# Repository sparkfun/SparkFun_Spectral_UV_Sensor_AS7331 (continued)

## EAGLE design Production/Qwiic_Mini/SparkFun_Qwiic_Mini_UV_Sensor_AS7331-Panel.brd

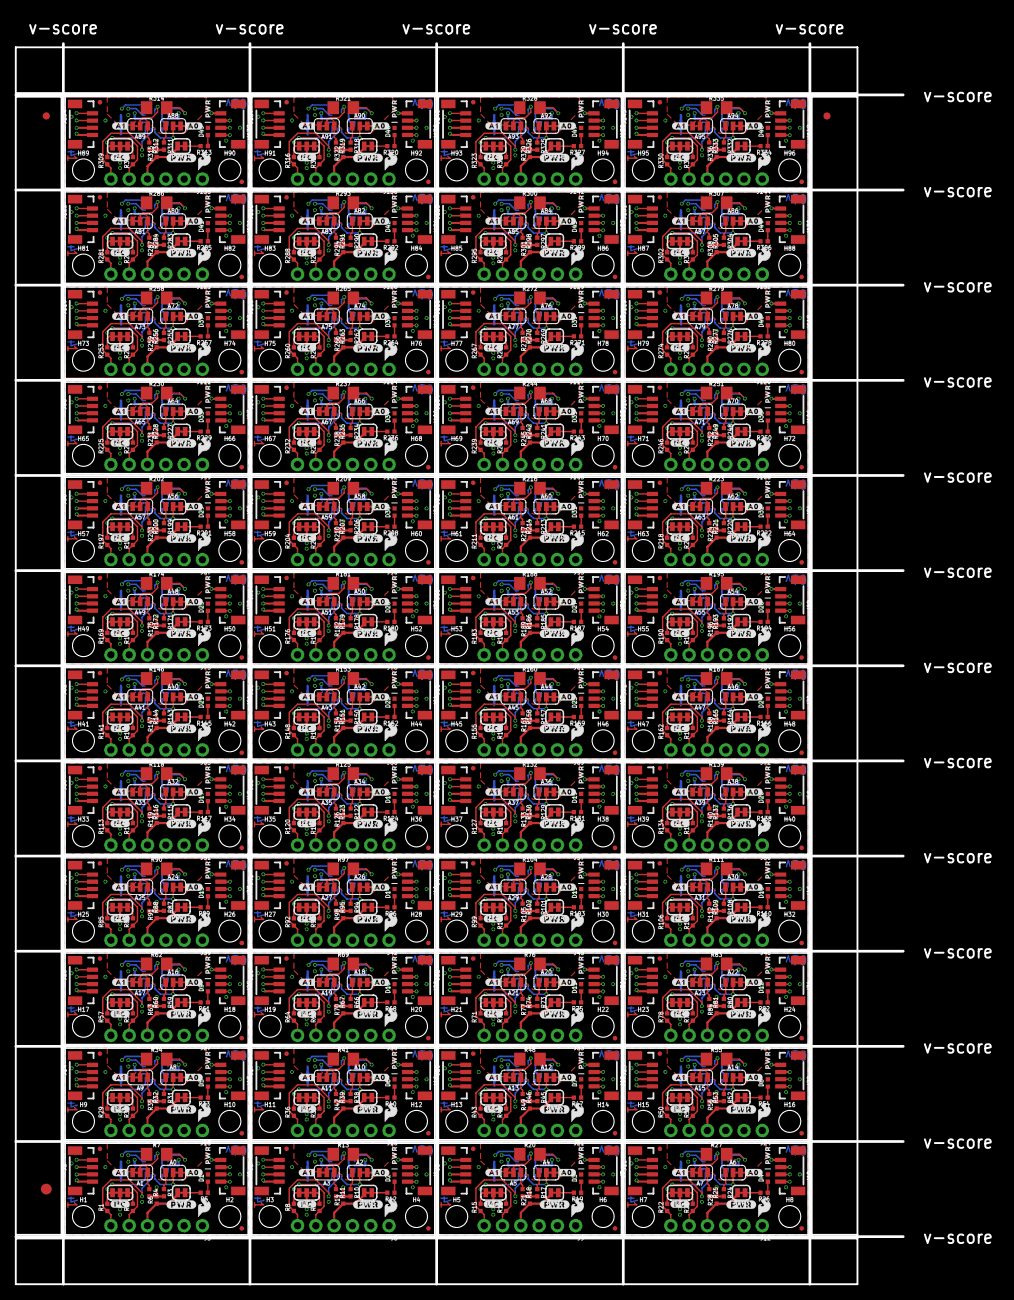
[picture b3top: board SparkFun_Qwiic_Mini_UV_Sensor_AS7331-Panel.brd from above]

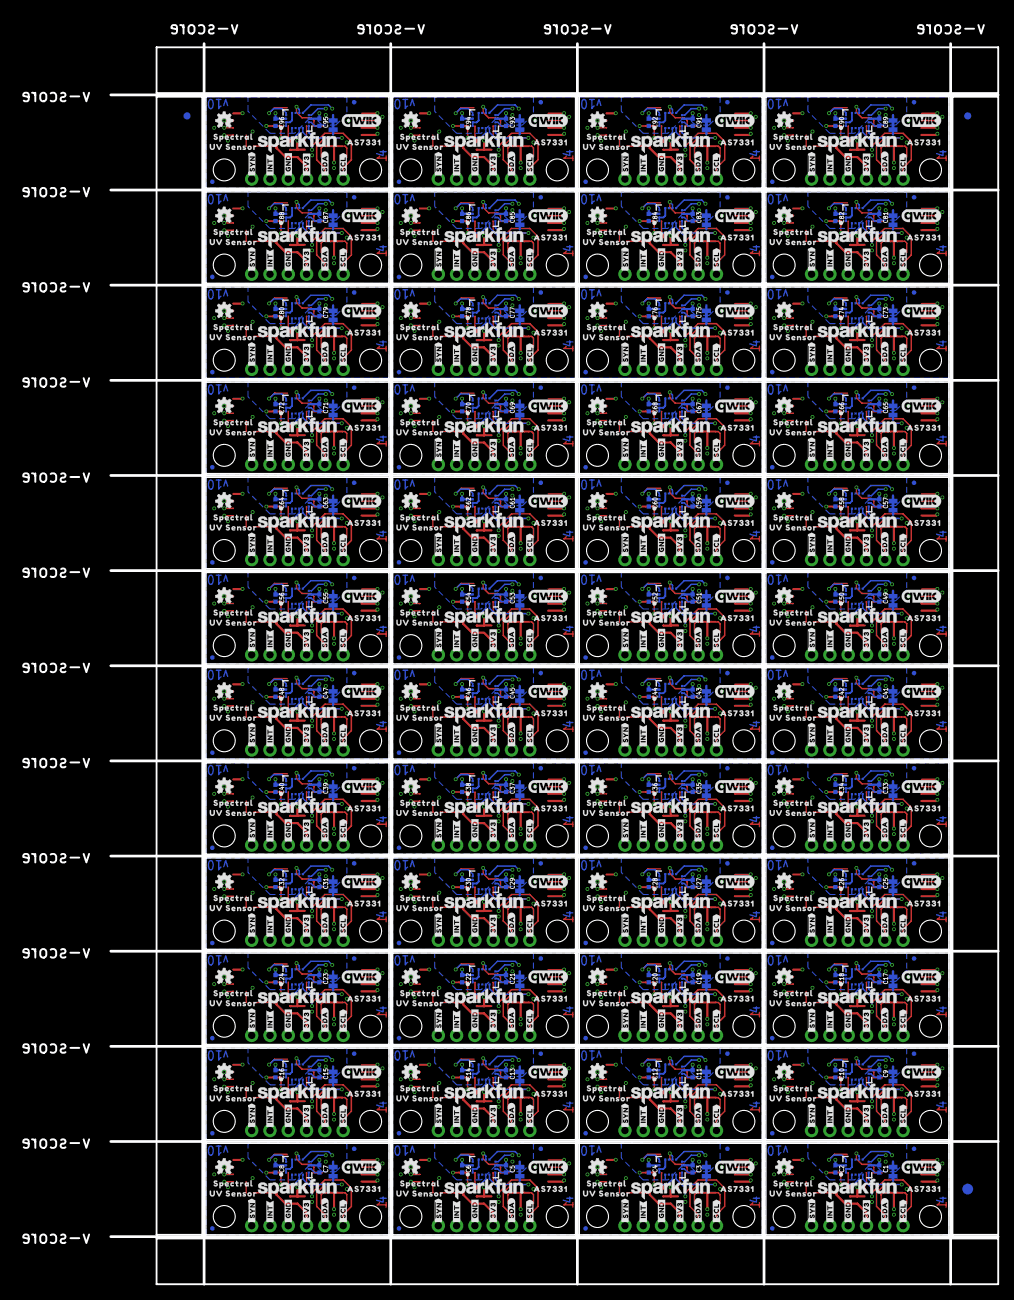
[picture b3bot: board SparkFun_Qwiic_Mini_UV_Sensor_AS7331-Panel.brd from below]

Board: 4 copper layers, 123.2 x 172.2 mm, 2070 parts (867 on the bottom side), 816 nets.

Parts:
A0, A1, A2, A3, A4, A5, A6, A7, A8, A9, A10, A11, A12, A13, A14, A15, A16, A17, A18, A19, A20, A21, A22, A23, A24, A25, A26, A27, A28, A29, A30, A31, A32, A33, A34, A35, A36, A37, A38, A39, A40, A41, A42, A43, A44, A45, A46, A47, A48, A49, A50, A51, A52, A53, A54, A55, A56, A57, A58, A59, A60, A61, A62, A63, A64, A65, A66, A67, A68, A69, A70, A71, A72, A73, A74, A75, A76, A77, A78, A79, A80, A81, A82, A83, A84, A85, A86, A87, A88, A89, A90, A91, A92, A93, A94, A95: JUMPER-SMT_3_1-NC_TRACE_SILK; SMT-JUMPER_3_1-NC_TRACE_SILK
C1, C2, C3, C4, C5, C6, C7, C8, C9, C10, C11, C12, C13, C14, C15, C16, C17, C18, C19, C20, C21, C22, C23, C24, C25, C26, C27, C28, C29, C30, C31, C32, C33, C34, C35, C36, C37, C38, C39, C40, C41, C42, C43, C44, C45, C46, C47, C48, C49, C50, C51, C52, C53, C54, C55, C56, C57, C58, C59, C60, C61, C62, C63, C64, C65, C66, C67, C68, C69, C70, C71, C72, C73, C74, C75, C76, C77, C78, C79, C80, C81, C82, C83, C84, C85, C86, C87, C88, C89, C90, C91, C92, C93, C94, C95, C96: 0.1uF; 0402-TIGHT
D1, D2, D3, D4, D5, D6, D7, D8, D9, D10, D11, D12, D13, D14, D15, D16, D17, D18, D19, D20, D21, D22, D23, D24, D25, D26, D27, D28, D29, D30, D31, D32, D33, D34, D35, D36, D37, D38, D39, D40, D41, D42, D43, D44, D45, D46, D47, D48: RED; LED-0402
E$1, E$2, E$3, E$4: FIDUCIAL-1X2
E$5, E$6: FIDUCIAL-1.5X3
FD1, FD2, FD3, FD4, FD5, FD6, FD7, FD8, FD9, FD10, FD11, FD12, FD13, FD14, FD15, FD16, FD17, FD18, FD19, FD20, FD21, FD22, FD23, FD24, FD25, FD26, FD27, FD28, FD29, FD30, FD31, FD32, FD33, FD34, FD35, FD36, FD37, FD38, FD39, FD40, FD41, FD42, FD43, FD44, FD45, FD46, FD47, FD48, FD49, FD50, FD51, FD52, FD53, FD54, FD55, FD56, FD57, FD58, FD59, FD60, FD61, FD62, FD63, FD64, FD65, FD66, FD67, FD68, FD69, FD70, FD71, FD72, FD73, FD74, FD75, FD76, FD77, FD78, FD79, FD80, FD81, FD82, FD83, FD84, FD85, FD86, FD87, FD88, FD89, FD90, FD91, FD92, FD93, FD94, FD95, FD96, FD97, FD98, FD99, FD100, FD101, FD102, FD103, FD104, FD105, FD106, FD107, FD108, FD109, FD110, FD111, FD112, FD113, FD114, FD115, FD116, FD117, FD118, FD119, FD120, FD121, FD122, FD123, FD124, FD125, FD126, FD127, FD128, FD129, FD130, FD131, FD132, FD133, FD134, FD135, FD136, FD137, FD138, FD139, FD140, FD141, FD142, FD143, FD144, FD145, FD146, FD147, FD148, FD149, FD150, FD151, FD152, FD153, FD154, FD155, FD156, FD157, FD158, FD159, FD160, FD161, FD162, FD163, FD164, FD165, FD166, FD167, FD168, FD169, FD170, FD171, FD172, FD173, FD174, FD175, FD176, FD177, FD178, FD179, FD180, FD181, FD182, FD183, FD184, FD185, FD186, FD187, FD188, FD189, FD190, FD191, FD192: FIDUCIALUFIDUCIAL; FIDUCIAL-MICRO
H1, H2, H3, H4, H5, H6, H7, H8, H9, H10, H11, H12, H13, H14, H15, H16, H17, H18, H19, H20, H21, H22, H23, H24, H25, H26, H27, H28, H29, H30, H31, H32, H33, H34, H35, H36, H37, H38, H39, H40, H41, H42, H43, H44, H45, H46, H47, H48, H49, H50, H51, H52, H53, H54, H55, H56, H57, H58, H59, H60, H61, H62, H63, H64, H65, H66, H67, H68, H69, H70, H71, H72, H73, H74, H75, H76, H77, H78, H79, H80, H81, H82, H83, H84, H85, H86, H87, H88, H89, H90, H91, H92, H93, H94, H95, H96: STAND-OFFTIGHT; STAND-OFF-TIGHT
I2C, I2C1, I2C2, I2C3, I2C4, I2C5, I2C6, I2C7, I2C8, I2C9, I2C10, I2C11, I2C12, I2C13, I2C14, I2C15, I2C16, I2C17, I2C18, I2C19, I2C20, I2C21, I2C22, I2C23, I2C24, I2C25, I2C26, I2C27, I2C28, I2C29, I2C30, I2C31, I2C32, I2C33, I2C34, I2C35, I2C36, I2C37, I2C38, I2C39, I2C40, I2C41, I2C42, I2C43, I2C44, I2C45, I2C46, I2C47: JUMPER-SMT_3_2-NC_TRACE_SILK; SMT-JUMPER_3_2-NC_TRACE_SILK
J1, J2, J4, J5, J7, J8, J10, J11, J13, J14, J16, J17, J19, J20, J22, J23, J25, J26, J28, J29, J31, J32, J34, J35, J37, J38, J40, J41, J43, J44, J46, J47, J49, J50, J52, J53, J55, J56, J58, J59, J61, J62, J64, J65, J67, J68, J70, J71, J73, J74, J76, J77, J79, J80, J82, J83, J85, J86, J88, J89, J91, J92, J94, J95, J97, J98, J100, J101, J103, J104, J106, J107, J109, J110, J112, J113, J115, J116, J118, J119, J121, J122, J124, J125, J127, J128, J130, J131, J133, J134, J136, J137, J139, J140, J142, J143: Qwiic Vert; JST04_1MM_VERT
J3, J6, J9, J12, J15, J18, J21, J24, J27, J30, J33, J36, J39, J42, J45, J48, J51, J54, J57, J60, J63, J66, J69, J72, J75, J78, J81, J84, J87, J90, J93, J96, J99, J102, J105, J108, J111, J114, J117, J120, J123, J126, J129, J132, J135, J138, J141, J144: 1X06_NO_SILK
LOGO1, LOGO5, LOGO9, LOGO13, LOGO17, LOGO21, LOGO25, LOGO29, LOGO33, LOGO37, LOGO41, LOGO45, LOGO49, LOGO53, LOGO57, LOGO61, LOGO65, LOGO69, LOGO73, LOGO77, LOGO81, LOGO85, LOGO89, LOGO93, LOGO97, LOGO101, LOGO105, LOGO109, LOGO113, LOGO117, LOGO121, LOGO125, LOGO129, LOGO133, LOGO137, LOGO141, LOGO145, LOGO149, LOGO153, LOGO157, LOGO161, LOGO165, LOGO169, LOGO173, LOGO177, LOGO181, LOGO185, LOGO189: SFE_LOGO_NAME.1_INCH; SFE_LOGO_NAME_.1
LOGO2, LOGO6, LOGO10, LOGO14, LOGO18, LOGO22, LOGO26, LOGO30, LOGO34, LOGO38, LOGO42, LOGO46, LOGO50, LOGO54, LOGO58, LOGO62, LOGO66, LOGO70, LOGO74, LOGO78, LOGO82, LOGO86, LOGO90, LOGO94, LOGO98, LOGO102, LOGO106, LOGO110, LOGO114, LOGO118, LOGO122, LOGO126, LOGO130, LOGO134, LOGO138, LOGO142, LOGO146, LOGO150, LOGO154, LOGO158, LOGO162, LOGO166, LOGO170, LOGO174, LOGO178, LOGO182, LOGO186, LOGO190: QWIIC_LOGO_CONNECTOR; QWIIC_5.5MM
LOGO3, LOGO7, LOGO11, LOGO15, LOGO19, LOGO23, LOGO27, LOGO31, LOGO35, LOGO39, LOGO43, LOGO47, LOGO51, LOGO55, LOGO59, LOGO63, LOGO67, LOGO71, LOGO75, LOGO79, LOGO83, LOGO87, LOGO91, LOGO95, LOGO99, LOGO103, LOGO107, LOGO111, LOGO115, LOGO119, LOGO123, LOGO127, LOGO131, LOGO135, LOGO139, LOGO143, LOGO147, LOGO151, LOGO155, LOGO159, LOGO163, LOGO167, LOGO171, LOGO175, LOGO179, LOGO183, LOGO187, LOGO191: OSHW-LOGOMINI; OSHW-LOGO-MINI
LOGO4, LOGO8, LOGO12, LOGO16, LOGO20, LOGO24, LOGO28, LOGO32, LOGO36, LOGO40, LOGO44, LOGO48, LOGO52, LOGO56, LOGO60, LOGO64, LOGO68, LOGO72, LOGO76, LOGO80, LOGO84, LOGO88, LOGO92, LOGO96, LOGO100, LOGO104, LOGO108, LOGO112, LOGO116, LOGO120, LOGO124, LOGO128, LOGO132, LOGO136, LOGO140, LOGO144, LOGO148, LOGO152, LOGO156, LOGO160, LOGO164, LOGO168, LOGO172, LOGO176, LOGO180, LOGO184, LOGO188, LOGO192: SFE_LOGO_FLAME.1_INCH; SFE_LOGO_FLAME_.1
PWR, PWR1, PWR2, PWR3, PWR4, PWR5, PWR6, PWR7, PWR8, PWR9, PWR10, PWR11, PWR12, PWR13, PWR14, PWR15, PWR16, PWR17, PWR18, PWR19, PWR20, PWR21, PWR22, PWR23, PWR24, PWR25, PWR26, PWR27, PWR28, PWR29, PWR30, PWR31, PWR32, PWR33, PWR34, PWR35, PWR36, PWR37, PWR38, PWR39, PWR40, PWR41, PWR42, PWR43, PWR44, PWR45, PWR46, PWR47: JUMPER-SMT_2_NC_TRACE_SILK; SMT-JUMPER_2_NC_TRACE_SILK
R1, R2, R5, R8, R9, R12, R15, R16, R19, R22, R23, R26, R29, R30, R33, R36, R37, R40, R43, R44, R47, R50, R51, R54, R57, R58, R61, R64, R65, R68, R71, R72, R75, R78, R79, R82, R85, R86, R89, R92, R93, R96, R99, R100, R103, R106, R107, R110, R113, R114, R117, R120, R121, R124, R127, R128, R131, R134, R135, R138, R141, R142, R145, R148, R149, R152, R155, R156, R159, R162, R163, R166, R169, R170, R173, R176, R177, R180, R183, R184, R187, R190, R191, R194, R197, R198, R201, R204, R205, R208, R211, R212, R215, R218, R219, R222, R225, R226, R229, R232, R233, R236, R239, R240, R243, R246, R247, R250, R253, R254, R257, R260, R261, R264, R267, R268, R271, R274, R275, R278, R281, R282, R285, R288, R289, R292, R295, R296, R299, R302, R303, R306, R309, R310, R313, R316, R317, R320, R323, R324, R327, R330, R331, R334: 2.2k; 0402-TIGHT
R3, R4, R10, R11, R17, R18, R24, R25, R31, R32, R38, R39, R45, R46, R52, R53, R59, R60, R66, R67, R73, R74, R80, R81, R87, R88, R94, R95, R101, R102, R108, R109, R115, R116, R122, R123, R129, R130, R136, R137, R143, R144, R150, R151, R157, R158, R164, R165, R171, R172, R178, R179, R185, R186, R192, R193, R199, R200, R206, R207, R213, R214, R220, R221, R227, R228, R234, R235, R241, R242, R248, R249, R255, R256, R262, R263, R269, R270, R276, R277, R283, R284, R290, R291, R297, R298, R304, R305, R311, R312, R318, R319, R325, R326, R332, R333: 10K; 0402-TIGHT
R6, R14, R21, R28, R35, R42, R49, R56, R63, R70, R77, R84, R91, R98, R105, R112, R119, R126, R133, R140, R147, R154, R161, R168, R175, R182, R189, R196, R203, R210, R217, R224, R231, R238, R245, R252, R259, R266, R273, R280, R287, R294, R301, R308, R315, R322, R329, R336: 10Ω; 0402-TIGHT
R7, R13, R20, R27, R34, R41, R48, R55, R62, R69, R76, R83, R90, R97, R104, R111, R118, R125, R132, R139, R146, R153, R160, R167, R174, R181, R188, R195, R202, R209, R216, R223, R230, R237, R244, R251, R258, R265, R272, R279, R286, R293, R300, R307, R314, R321, R328, R335: 3.3M; 1206
SUPPLYTIE1, SUPPLYTIE2, SUPPLYTIE3, SUPPLYTIE4, SUPPLYTIE5, SUPPLYTIE6, SUPPLYTIE7, SUPPLYTIE8, SUPPLYTIE9, SUPPLYTIE10, SUPPLYTIE11, SUPPLYTIE12, SUPPLYTIE13, SUPPLYTIE14, SUPPLYTIE15, SUPPLYTIE16, SUPPLYTIE17, SUPPLYTIE18, SUPPLYTIE19, SUPPLYTIE20, SUPPLYTIE21, SUPPLYTIE22, SUPPLYTIE23, SUPPLYTIE24, SUPPLYTIE25, SUPPLYTIE26, SUPPLYTIE27, SUPPLYTIE28, SUPPLYTIE29, SUPPLYTIE30, SUPPLYTIE31, SUPPLYTIE32, SUPPLYTIE33, SUPPLYTIE34, SUPPLYTIE35, SUPPLYTIE36, SUPPLYTIE37, SUPPLYTIE38, SUPPLYTIE39, SUPPLYTIE40, SUPPLYTIE41, SUPPLYTIE42, SUPPLYTIE43, SUPPLYTIE44, SUPPLYTIE45, SUPPLYTIE46, SUPPLYTIE47, SUPPLYTIE48: 2PT_GND_TIE
U1, U2, U3, U4, U5, U6, U7, U8, U9, U10, U11, U12, U13, U14, U15, U16, U17, U18, U19, U20, U21, U22, U23, U24, U25, U26, U27, U28, U29, U30, U31, U32, U33, U34, U35, U36, U37, U38, U39, U40, U41, U42, U43, U44, U45, U46, U47, U48: AS7331; OLGA16
U$1, U$6, U$29, U$43, U$57, U$71, U$85, U$99, U$113, U$127, U$141, U$155, U$169, U$183, U$197, U$211, U$225, U$239, U$253, U$267, U$281, U$295, U$309, U$323, U$337, U$351, U$365, U$379, U$393, U$407, U$421, U$435, U$449, U$463, U$477, U$491, U$505, U$519, U$533, U$547, U$561, U$575, U$589, U$603, U$617, U$631, U$645, U$659: #I�C#0
U$2, U$7, U$30, U$44, U$58, U$72, U$86, U$100, U$114, U$128, U$142, U$156, U$170, U$184, U$198, U$212, U$226, U$240, U$254, U$268, U$282, U$296, U$310, U$324, U$338, U$352, U$366, U$380, U$394, U$408, U$422, U$436, U$450, U$464, U$478, U$492, U$506, U$520, U$534, U$548, U$562, U$576, U$590, U$604, U$618, U$632, U$646, U$660: #A0#0
U$3, U$8, U$31, U$45, U$59, U$73, U$87, U$101, U$115, U$129, U$143, U$157, U$171, U$185, U$199, U$213, U$227, U$241, U$255, U$269, U$283, U$297, U$311, U$325, U$339, U$353, U$367, U$381, U$395, U$409, U$423, U$437, U$451, U$465, U$479, U$493, U$507, U$521, U$535, U$549, U$563, U$577, U$591, U$605, U$619, U$633, U$647, U$661: #A1#0
U$4, U$10, U$32, U$46, U$60, U$74, U$88, U$102, U$116, U$130, U$144, U$158, U$172, U$186, U$200, U$214, U$228, U$242, U$256, U$270, U$284, U$298, U$312, U$326, U$340, U$354, U$368, U$382, U$396, U$410, U$424, U$438, U$452, U$466, U$480, U$494, U$508, U$522, U$536, U$550, U$564, U$578, U$592, U$606, U$620, U$634, U$648, U$662: PWR0
U$5, U$11, U$33, U$47, U$61, U$75, U$89, U$103, U$117, U$131, U$145, U$159, U$173, U$187, U$201, U$215, U$229, U$243, U$257, U$271, U$285, U$299, U$313, U$327, U$341, U$355, U$369, U$383, U$397, U$411, U$425, U$439, U$453, U$467, U$481, U$495, U$509, U$523, U$537, U$551, U$565, U$579, U$593, U$607, U$621, U$635, U$649, U$663: #_SCL#0
U$9, U$24, U$38, U$52, U$66, U$80, U$94, U$108, U$122, U$136, U$150, U$164, U$178, U$192, U$206, U$220, U$234, U$248, U$262, U$276, U$290, U$304, U$318, U$332, U$346, U$360, U$374, U$388, U$402, U$416, U$430, U$444, U$458, U$472, U$486, U$500, U$514, U$528, U$542, U$556, U$570, U$584, U$598, U$612, U$626, U$640, U$654, U$668: #PWR#0
U$12, U$16, U$34, U$48, U$62, U$76, U$90, U$104, U$118, U$132, U$146, U$160, U$174, U$188, U$202, U$216, U$230, U$244, U$258, U$272, U$286, U$300, U$314, U$328, U$342, U$356, U$370, U$384, U$398, U$412, U$426, U$440, U$454, U$468, U$482, U$496, U$510, U$524, U$538, U$552, U$566, U$580, U$594, U$608, U$622, U$636, U$650, U$664: #_SDA#0
U$13, U$19, U$35, U$49, U$63, U$77, U$91, U$105, U$119, U$133, U$147, U$161, U$175, U$189, U$203, U$217, U$231, U$245, U$259, U$273, U$287, U$301, U$315, U$329, U$343, U$357, U$371, U$385, U$399, U$413, U$427, U$441, U$455, U$469, U$483, U$497, U$511, U$525, U$539, U$553, U$567, U$581, U$595, U$609, U$623, U$637, U$651, U$665: #_3V3#0
U$14, U$22, U$36, U$50, U$64, U$78, U$92, U$106, U$120, U$134, U$148, U$162, U$176, U$190, U$204, U$218, U$232, U$246, U$260, U$274, U$288, U$302, U$316, U$330, U$344, U$358, U$372, U$386, U$400, U$414, U$428, U$442, U$456, U$470, U$484, U$498, U$512, U$526, U$540, U$554, U$568, U$582, U$596, U$610, U$624, U$638, U$652, U$666: #_GND#0
U$15, U$23, U$37, U$51, U$65, U$79, U$93, U$107, U$121, U$135, U$149, U$163, U$177, U$191, U$205, U$219, U$233, U$247, U$261, U$275, U$289, U$303, U$317, U$331, U$345, U$359, U$373, U$387, U$401, U$415, U$429, U$443, U$457, U$471, U$485, U$499, U$513, U$527, U$541, U$555, U$569, U$583, U$597, U$611, U$625, U$639, U$653, U$667: #_INT#0
U$17, U$25, U$39, U$53, U$67, U$81, U$95, U$109, U$123, U$137, U$151, U$165, U$179, U$193, U$207, U$221, U$235, U$249, U$263, U$277, U$291, U$305, U$319, U$333, U$347, U$361, U$375, U$389, U$403, U$417, U$431, U$445, U$459, U$473, U$487, U$501, U$515, U$529, U$543, U$557, U$571, U$585, U$599, U$613, U$627, U$641, U$655, U$669: UV_SENSOR0
U$18, U$26, U$40, U$54, U$68, U$82, U$96, U$110, U$124, U$138, U$152, U$166, U$180, U$194, U$208, U$222, U$236, U$250, U$264, U$278, U$292, U$306, U$320, U$334, U$348, U$362, U$376, U$390, U$404, U$418, U$432, U$446, U$460, U$474, U$488, U$502, U$516, U$530, U$544, U$558, U$572, U$586, U$600, U$614, U$628, U$642, U$656, U$670: AS73310
U$20, U$27, U$41, U$55, U$69, U$83, U$97, U$111, U$125, U$139, U$153, U$167, U$181, U$195, U$209, U$223, U$237, U$251, U$265, U$279, U$293, U$307, U$321, U$335, U$349, U$363, U$377, U$391, U$405, U$419, U$433, U$447, U$461, U$475, U$489, U$503, U$517, U$531, U$545, U$559, U$573, U$587, U$601, U$615, U$629, U$643, U$657, U$671: SPECTRAL0
U$21, U$28, U$42, U$56, U$70, U$84, U$98, U$112, U$126, U$140, U$154, U$168, U$182, U$196, U$210, U$224, U$238, U$252, U$266, U$280, U$294, U$308, U$322, U$336, U$350, U$364, U$378, U$392, U$406, U$420, U$434, U$448, U$462, U$476, U$490, U$504, U$518, U$532, U$546, U$560, U$574, U$588, U$602, U$616, U$630, U$644, U$658, U$672: #_#SYN##0

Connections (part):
3.3V: C1.1, I2C.2, J1.2, J2.2, J3.4, PWR.2, R6.1, U1.10
3.3V1: C3.1, I2C1.2, J4.2, J5.2, J6.4, PWR1.2, R14.1, U2.10
3.3V2: C5.1, I2C2.2, J7.2, J8.2, J9.4, PWR2.2, R21.1, U3.10
3.3V3: C7.1, I2C3.2, J10.2, J11.2, J12.4, PWR3.2, R28.1, U4.10
3.3V4: C9.1, I2C4.2, J13.2, J14.2, J15.4, PWR4.2, R35.1, U5.10
3.3V5: C11.1, I2C5.2, J16.2, J17.2, J18.4, PWR5.2, R42.1, U6.10
3.3V6: C13.1, I2C6.2, J19.2, J20.2, J21.4, PWR6.2, R49.1, U7.10
3.3V7: C15.1, I2C7.2, J22.2, J23.2, J24.4, PWR7.2, R56.1, U8.10
3.3V8: C17.1, I2C8.2, J25.2, J26.2, J27.4, PWR8.2, R63.1, U9.10
3.3V9: C19.1, I2C9.2, J28.2, J29.2, J30.4, PWR9.2, R70.1, U10.10
3.3V10: C21.1, I2C10.2, J31.2, J32.2, J33.4, PWR10.2, R77.1, U11.10
3.3V11: C23.1, I2C11.2, J34.2, J35.2, J36.4, PWR11.2, R84.1, U12.10
3.3V12: C25.1, I2C12.2, J37.2, J38.2, J39.4, PWR12.2, R91.1, U13.10
3.3V13: C27.1, I2C13.2, J40.2, J41.2, J42.4, PWR13.2, R98.1, U14.10
3.3V14: C29.1, I2C14.2, J43.2, J44.2, J45.4, PWR14.2, R105.1, U15.10
3.3V15: C31.1, I2C15.2, J46.2, J47.2, J48.4, PWR15.2, R112.1, U16.10
3.3V16: C33.1, I2C16.2, J49.2, J50.2, J51.4, PWR16.2, R119.1, U17.10
3.3V17: C35.1, I2C17.2, J52.2, J53.2, J54.4, PWR17.2, R126.1, U18.10
3.3V18: C37.1, I2C18.2, J55.2, J56.2, J57.4, PWR18.2, R133.1, U19.10
3.3V19: C39.1, I2C19.2, J58.2, J59.2, J60.4, PWR19.2, R140.1, U20.10
3.3V20: C41.1, I2C20.2, J61.2, J62.2, J63.4, PWR20.2, R147.1, U21.10
3.3V21: C43.1, I2C21.2, J64.2, J65.2, J66.4, PWR21.2, R154.1, U22.10
3.3V22: C45.1, I2C22.2, J67.2, J68.2, J69.4, PWR22.2, R161.1, U23.10
3.3V23: C47.1, I2C23.2, J70.2, J71.2, J72.4, PWR23.2, R168.1, U24.10
3.3V24: C49.1, I2C24.2, J73.2, J74.2, J75.4, PWR24.2, R175.1, U25.10
3.3V25: C51.1, I2C25.2, J76.2, J77.2, J78.4, PWR25.2, R182.1, U26.10
3.3V26: C53.1, I2C26.2, J79.2, J80.2, J81.4, PWR26.2, R189.1, U27.10
3.3V27: C55.1, I2C27.2, J82.2, J83.2, J84.4, PWR27.2, R196.1, U28.10
3.3V28: C57.1, I2C28.2, J85.2, J86.2, J87.4, PWR28.2, R203.1, U29.10
3.3V29: C59.1, I2C29.2, J88.2, J89.2, J90.4, PWR29.2, R210.1, U30.10
3.3V30: C61.1, I2C30.2, J91.2, J92.2, J93.4, PWR30.2, R217.1, U31.10
3.3V31: C63.1, I2C31.2, J94.2, J95.2, J96.4, PWR31.2, R224.1, U32.10
3.3V32: C65.1, I2C32.2, J97.2, J98.2, J99.4, PWR32.2, R231.1, U33.10
3.3V33: C67.1, I2C33.2, J100.2, J101.2, J102.4, PWR33.2, R238.1, U34.10
3.3V34: C69.1, I2C34.2, J103.2, J104.2, J105.4, PWR34.2, R245.1, U35.10
3.3V35: C71.1, I2C35.2, J106.2, J107.2, J108.4, PWR35.2, R252.1, U36.10
3.3V36: C73.1, I2C36.2, J109.2, J110.2, J111.4, PWR36.2, R259.1, U37.10
3.3V37: C75.1, I2C37.2, J112.2, J113.2, J114.4, PWR37.2, R266.1, U38.10
3.3V38: C77.1, I2C38.2, J115.2, J116.2, J117.4, PWR38.2, R273.1, U39.10
3.3V39: C79.1, I2C39.2, J118.2, J119.2, J120.4, PWR39.2, R280.1, U40.10
3.3V40: C81.1, I2C40.2, J121.2, J122.2, J123.4, PWR40.2, R287.1, U41.10
3.3V41: C83.1, I2C41.2, J124.2, J125.2, J126.4, PWR41.2, R294.1, U42.10
3.3V42: C85.1, I2C42.2, J127.2, J128.2, J129.4, PWR42.2, R301.1, U43.10
3.3V43: C87.1, I2C43.2, J130.2, J131.2, J132.4, PWR43.2, R308.1, U44.10
3.3V44: C89.1, I2C44.2, J133.2, J134.2, J135.4, PWR44.2, R315.1, U45.10
3.3V45: C91.1, I2C45.2, J136.2, J137.2, J138.4, PWR45.2, R322.1, U46.10
3.3V46: C93.1, I2C46.2, J139.2, J140.2, J141.4, PWR46.2, R329.1, U47.10
3.3V47: C95.1, I2C47.2, J142.2, J143.2, J144.4, PWR47.2, R336.1, U48.10
!SYNC: J3.1, U1.8
!SYNC1: J6.1, U2.8
!SYNC2: J9.1, U3.8
!SYNC3: J12.1, U4.8
!SYNC4: J15.1, U5.8
!SYNC5: J18.1, U6.8
!SYNC6: J21.1, U7.8
!SYNC7: J24.1, U8.8
!SYNC8: J27.1, U9.8
!SYNC9: J30.1, U10.8
!SYNC10: J33.1, U11.8
!SYNC11: J36.1, U12.8
!SYNC12: J39.1, U13.8
!SYNC13: J42.1, U14.8
!SYNC14: J45.1, U15.8
!SYNC15: J48.1, U16.8
!SYNC16: J51.1, U17.8
!SYNC17: J54.1, U18.8
!SYNC18: J57.1, U19.8
!SYNC19: J60.1, U20.8
!SYNC20: J63.1, U21.8
!SYNC21: J66.1, U22.8
!SYNC22: J69.1, U23.8
!SYNC23: J72.1, U24.8
!SYNC24: J75.1, U25.8
!SYNC25: J78.1, U26.8
!SYNC26: J81.1, U27.8
!SYNC27: J84.1, U28.8
!SYNC28: J87.1, U29.8
!SYNC29: J90.1, U30.8
!SYNC30: J93.1, U31.8
!SYNC31: J96.1, U32.8
!SYNC32: J99.1, U33.8
!SYNC33: J102.1, U34.8
!SYNC34: J105.1, U35.8
!SYNC35: J108.1, U36.8
!SYNC36: J111.1, U37.8
!SYNC37: J114.1, U38.8
!SYNC38: J117.1, U39.8
!SYNC39: J120.1, U40.8
!SYNC40: J123.1, U41.8
!SYNC41: J126.1, U42.8
!SYNC42: J129.1, U43.8
!SYNC43: J132.1, U44.8
!SYNC44: J135.1, U45.8
!SYNC45: J138.1, U46.8
!SYNC46: J141.1, U47.8
!SYNC47: J144.1, U48.8
A0: A0.2, U1.14
A1: A1.2, U1.7
A2: A2.2, U2.14
A3: A3.2, U2.7
A4: A4.2, U3.14
A5: A5.2, U3.7
A6: A6.2, U4.14
A7: A7.2, U4.7
A8: A8.2, U5.14
A9: A9.2, U5.7
A10: A10.2, U6.14
A11: A11.2, U6.7
A12: A12.2, U7.14
A13: A13.2, U7.7
A14: A14.2, U8.14
A15: A15.2, U8.7
A16: A16.2, U9.14
A17: A17.2, U9.7
A18: A18.2, U10.14
A19: A19.2, U10.7
A20: A20.2, U11.14
A21: A21.2, U11.7
A22: A22.2, U12.14
A23: A23.2, U12.7
A24: A24.2, U13.14
A25: A25.2, U13.7
A26: A26.2, U14.14
A27: A27.2, U14.7
A28: A28.2, U15.14
A29: A29.2, U15.7
A30: A30.2, U16.14
A31: A31.2, U16.7
A32: A32.2, U17.14
A33: A33.2, U17.7
A34: A34.2, U18.14
A35: A35.2, U18.7
A36: A36.2, U19.14
A37: A37.2, U19.7
A38: A38.2, U20.14
A39: A39.2, U20.7
A40: A40.2, U21.14
A41: A41.2, U21.7
A42: A42.2, U22.14
A43: A43.2, U22.7
A44: A44.2, U23.14
A45: A45.2, U23.7
A46: A46.2, U24.14
A47: A47.2, U24.7
A48: A48.2, U25.14
A49: A49.2, U25.7
A50: A50.2, U26.14
A51: A51.2, U26.7
A52: A52.2, U27.14
A53: A53.2, U27.7
A54: A54.2, U28.14
A55: A55.2, U28.7
A56: A56.2, U29.14
A57: A57.2, U29.7
A58: A58.2, U30.14
A59: A59.2, U30.7
A60: A60.2, U31.14
A61: A61.2, U31.7
A62: A62.2, U32.14
A63: A63.2, U32.7
A64: A64.2, U33.14
A65: A65.2, U33.7
A66: A66.2, U34.14
A67: A67.2, U34.7
A68: A68.2, U35.14
A69: A69.2, U35.7
A70: A70.2, U36.14
A71: A71.2, U36.7
A72: A72.2, U37.14
A73: A73.2, U37.7
A74: A74.2, U38.14
A75: A75.2, U38.7
A76: A76.2, U39.14
A77: A77.2, U39.7
A78: A78.2, U40.14
A79: A79.2, U40.7
A80: A80.2, U41.14
A81: A81.2, U41.7
A82: A82.2, U42.14
A83: A83.2, U42.7
A84: A84.2, U43.14
A85: A85.2, U43.7
A86: A86.2, U44.14
A87: A87.2, U44.7
A88: A88.2, U45.14
A89: A89.2, U45.7
A90: A90.2, U46.14
A91: A91.2, U46.7
A92: A92.2, U47.14
A93: A93.2, U47.7
A94: A94.2, U48.14
A95: A95.2, U48.7
AGND: A0.3, A1.3, C2.2, R7.1, SUPPLYTIE1.P$2, U1.1, U1.2, U1.5, U1.6, U1.15, U1.16
AGND1: A2.3, A3.3, C4.2, R13.1, SUPPLYTIE2.P$2, U2.1, U2.2, U2.5, U2.6, U2.15, U2.16
AGND2: A4.3, A5.3, C6.2, R20.1, SUPPLYTIE3.P$2, U3.1, U3.2, U3.5, U3.6, U3.15, U3.16
AGND3: A6.3, A7.3, C8.2, R27.1, SUPPLYTIE4.P$2, U4.1, U4.2, U4.5, U4.6, U4.15, U4.16
AGND4: A8.3, A9.3, C10.2, R34.1, SUPPLYTIE5.P$2, U5.1, U5.2, U5.5, U5.6, U5.15, U5.16
AGND5: A10.3, A11.3, C12.2, R41.1, SUPPLYTIE6.P$2, U6.1, U6.2, U6.5, U6.6, U6.15, U6.16
AGND6: A12.3, A13.3, C14.2, R48.1, SUPPLYTIE7.P$2, U7.1, U7.2, U7.5, U7.6, U7.15, U7.16
AGND7: A14.3, A15.3, C16.2, R55.1, SUPPLYTIE8.P$2, U8.1, U8.2, U8.5, U8.6, U8.15, U8.16
AGND8: A16.3, A17.3, C18.2, R62.1, SUPPLYTIE9.P$2, U9.1, U9.2, U9.5, U9.6, U9.15, U9.16
AGND9: A18.3, A19.3, C20.2, R69.1, SUPPLYTIE10.P$2, U10.1, U10.2, U10.5, U10.6, U10.15, U10.16
AGND10: A20.3, A21.3, C22.2, R76.1, SUPPLYTIE11.P$2, U11.1, U11.2, U11.5, U11.6, U11.15, U11.16
AGND11: A22.3, A23.3, C24.2, R83.1, SUPPLYTIE12.P$2, U12.1, U12.2, U12.5, U12.6, U12.15, U12.16
AGND12: A24.3, A25.3, C26.2, R90.1, SUPPLYTIE13.P$2, U13.1, U13.2, U13.5, U13.6, U13.15, U13.16
AGND13: A26.3, A27.3, C28.2, R97.1, SUPPLYTIE14.P$2, U14.1, U14.2, U14.5, U14.6, U14.15, U14.16
AGND14: A28.3, A29.3, C30.2, R104.1, SUPPLYTIE15.P$2, U15.1, U15.2, U15.5, U15.6, U15.15, U15.16
AGND15: A30.3, A31.3, C32.2, R111.1, SUPPLYTIE16.P$2, U16.1, U16.2, U16.5, U16.6, U16.15, U16.16
AGND16: A32.3, A33.3, C34.2, R118.1, SUPPLYTIE17.P$2, U17.1, U17.2, U17.5, U17.6, U17.15, U17.16
AGND17: A34.3, A35.3, C36.2, R125.1, SUPPLYTIE18.P$2, U18.1, U18.2, U18.5, U18.6, U18.15, U18.16
AGND18: A36.3, A37.3, C38.2, R132.1, SUPPLYTIE19.P$2, U19.1, U19.2, U19.5, U19.6, U19.15, U19.16
AGND19: A38.3, A39.3, C40.2, R139.1, SUPPLYTIE20.P$2, U20.1, U20.2, U20.5, U20.6, U20.15, U20.16
AGND20: A40.3, A41.3, C42.2, R146.1, SUPPLYTIE21.P$2, U21.1, U21.2, U21.5, U21.6, U21.15, U21.16
AGND21: A42.3, A43.3, C44.2, R153.1, SUPPLYTIE22.P$2, U22.1, U22.2, U22.5, U22.6, U22.15, U22.16
AGND22: A44.3, A45.3, C46.2, R160.1, SUPPLYTIE23.P$2, U23.1, U23.2, U23.5, U23.6, U23.15, U23.16
AGND23: A46.3, A47.3, C48.2, R167.1, SUPPLYTIE24.P$2, U24.1, U24.2, U24.5, U24.6, U24.15, U24.16
AGND24: A48.3, A49.3, C50.2, R174.1, SUPPLYTIE25.P$2, U25.1, U25.2, U25.5, U25.6, U25.15, U25.16
AGND25: A50.3, A51.3, C52.2, R181.1, SUPPLYTIE26.P$2, U26.1, U26.2, U26.5, U26.6, U26.15, U26.16
AGND26: A52.3, A53.3, C54.2, R188.1, SUPPLYTIE27.P$2, U27.1, U27.2, U27.5, U27.6, U27.15, U27.16
AGND27: A54.3, A55.3, C56.2, R195.1, SUPPLYTIE28.P$2, U28.1, U28.2, U28.5, U28.6, U28.15, U28.16
AGND28: A56.3, A57.3, C58.2, R202.1, SUPPLYTIE29.P$2, U29.1, U29.2, U29.5, U29.6, U29.15, U29.16
AGND29: A58.3, A59.3, C60.2, R209.1, SUPPLYTIE30.P$2, U30.1, U30.2, U30.5, U30.6, U30.15, U30.16
AGND30: A60.3, A61.3, C62.2, R216.1, SUPPLYTIE31.P$2, U31.1, U31.2, U31.5, U31.6, U31.15, U31.16
AGND31: A62.3, A63.3, C64.2, R223.1, SUPPLYTIE32.P$2, U32.1, U32.2, U32.5, U32.6, U32.15, U32.16
AGND32: A64.3, A65.3, C66.2, R230.1, SUPPLYTIE33.P$2, U33.1, U33.2, U33.5, U33.6, U33.15, U33.16
AGND33: A66.3, A67.3, C68.2, R237.1, SUPPLYTIE34.P$2, U34.1, U34.2, U34.5, U34.6, U34.15, U34.16
AGND34: A68.3, A69.3, C70.2, R244.1, SUPPLYTIE35.P$2, U35.1, U35.2, U35.5, U35.6, U35.15, U35.16
AGND35: A70.3, A71.3, C72.2, R251.1, SUPPLYTIE36.P$2, U36.1, U36.2, U36.5, U36.6, U36.15, U36.16
AGND36: A72.3, A73.3, C74.2, R258.1, SUPPLYTIE37.P$2, U37.1, U37.2, U37.5, U37.6, U37.15, U37.16
AGND37: A74.3, A75.3, C76.2, R265.1, SUPPLYTIE38.P$2, U38.1, U38.2, U38.5, U38.6, U38.15, U38.16
AGND38: A76.3, A77.3, C78.2, R272.1, SUPPLYTIE39.P$2, U39.1, U39.2, U39.5, U39.6, U39.15, U39.16
AGND39: A78.3, A79.3, C80.2, R279.1, SUPPLYTIE40.P$2, U40.1, U40.2, U40.5, U40.6, U40.15, U40.16
AGND40: A80.3, A81.3, C82.2, R286.1, SUPPLYTIE41.P$2, U41.1, U41.2, U41.5, U41.6, U41.15, U41.16
AGND41: A82.3, A83.3, C84.2, R293.1, SUPPLYTIE42.P$2, U42.1, U42.2, U42.5, U42.6, U42.15, U42.16
AGND42: A84.3, A85.3, C86.2, R300.1, SUPPLYTIE43.P$2, U43.1, U43.2, U43.5, U43.6, U43.15, U43.16
AGND43: A86.3, A87.3, C88.2, R307.1, SUPPLYTIE44.P$2, U44.1, U44.2, U44.5, U44.6, U44.15, U44.16
AGND44: A88.3, A89.3, C90.2, R314.1, SUPPLYTIE45.P$2, U45.1, U45.2, U45.5, U45.6, U45.15, U45.16
AGND45: A90.3, A91.3, C92.2, R321.1, SUPPLYTIE46.P$2, U46.1, U46.2, U46.5, U46.6, U46.15, U46.16
AGND46: A92.3, A93.3, C94.2, R328.1, SUPPLYTIE47.P$2, U47.1, U47.2, U47.5, U47.6, U47.15, U47.16
AGND47: A94.3, A95.3, C96.2, R335.1, SUPPLYTIE48.P$2, U48.1, U48.2, U48.5, U48.6, U48.15, U48.16
GND: C1.2, D1.C, J1.1, J2.1, J3.3, SUPPLYTIE1.P$1, U1.11
GND1: C3.2, D2.C, J4.1, J5.1, J6.3, SUPPLYTIE2.P$1, U2.11
GND2: C5.2, D3.C, J7.1, J8.1, J9.3, SUPPLYTIE3.P$1, U3.11
GND3: C7.2, D4.C, J10.1, J11.1, J12.3, SUPPLYTIE4.P$1, U4.11
GND4: C9.2, D5.C, J13.1, J14.1, J15.3, SUPPLYTIE5.P$1, U5.11
GND5: C11.2, D6.C, J16.1, J17.1, J18.3, SUPPLYTIE6.P$1, U6.11
GND6: C13.2, D7.C, J19.1, J20.1, J21.3, SUPPLYTIE7.P$1, U7.11
GND7: C15.2, D8.C, J22.1, J23.1, J24.3, SUPPLYTIE8.P$1, U8.11
GND8: C17.2, D9.C, J25.1, J26.1, J27.3, SUPPLYTIE9.P$1, U9.11
GND9: C19.2, D10.C, J28.1, J29.1, J30.3, SUPPLYTIE10.P$1, U10.11
GND10: C21.2, D11.C, J31.1, J32.1, J33.3, SUPPLYTIE11.P$1, U11.11
GND11: C23.2, D12.C, J34.1, J35.1, J36.3, SUPPLYTIE12.P$1, U12.11
GND12: C25.2, D13.C, J37.1, J38.1, J39.3, SUPPLYTIE13.P$1, U13.11
GND13: C27.2, D14.C, J40.1, J41.1, J42.3, SUPPLYTIE14.P$1, U14.11
GND14: C29.2, D15.C, J43.1, J44.1, J45.3, SUPPLYTIE15.P$1, U15.11
GND15: C31.2, D16.C, J46.1, J47.1, J48.3, SUPPLYTIE16.P$1, U16.11
GND16: C33.2, D17.C, J49.1, J50.1, J51.3, SUPPLYTIE17.P$1, U17.11
GND17: C35.2, D18.C, J52.1, J53.1, J54.3, SUPPLYTIE18.P$1, U18.11
GND18: C37.2, D19.C, J55.1, J56.1, J57.3, SUPPLYTIE19.P$1, U19.11
GND19: C39.2, D20.C, J58.1, J59.1, J60.3, SUPPLYTIE20.P$1, U20.11
GND20: C41.2, D21.C, J61.1, J62.1, J63.3, SUPPLYTIE21.P$1, U21.11
GND21: C43.2, D22.C, J64.1, J65.1, J66.3, SUPPLYTIE22.P$1, U22.11
GND22: C45.2, D23.C, J67.1, J68.1, J69.3, SUPPLYTIE23.P$1, U23.11
GND23: C47.2, D24.C, J70.1, J71.1, J72.3, SUPPLYTIE24.P$1, U24.11
GND24: C49.2, D25.C, J73.1, J74.1, J75.3, SUPPLYTIE25.P$1, U25.11
GND25: C51.2, D26.C, J76.1, J77.1, J78.3, SUPPLYTIE26.P$1, U26.11
GND26: C53.2, D27.C, J79.1, J80.1, J81.3, SUPPLYTIE27.P$1, U27.11
GND27: C55.2, D28.C, J82.1, J83.1, J84.3, SUPPLYTIE28.P$1, U28.11
GND28: C57.2, D29.C, J85.1, J86.1, J87.3, SUPPLYTIE29.P$1, U29.11
GND29: C59.2, D30.C, J88.1, J89.1, J90.3, SUPPLYTIE30.P$1, U30.11
GND30: C61.2, D31.C, J91.1, J92.1, J93.3, SUPPLYTIE31.P$1, U31.11
GND31: C63.2, D32.C, J94.1, J95.1, J96.3, SUPPLYTIE32.P$1, U32.11
GND32: C65.2, D33.C, J97.1, J98.1, J99.3, SUPPLYTIE33.P$1, U33.11
GND33: C67.2, D34.C, J100.1, J101.1, J102.3, SUPPLYTIE34.P$1, U34.11
GND34: C69.2, D35.C, J103.1, J104.1, J105.3, SUPPLYTIE35.P$1, U35.11
GND35: C71.2, D36.C, J106.1, J107.1, J108.3, SUPPLYTIE36.P$1, U36.11
GND36: C73.2, D37.C, J109.1, J110.1, J111.3, SUPPLYTIE37.P$1, U37.11
GND37: C75.2, D38.C, J112.1, J113.1, J114.3, SUPPLYTIE38.P$1, U38.11
GND38: C77.2, D39.C, J115.1, J116.1, J117.3, SUPPLYTIE39.P$1, U39.11
GND39: C79.2, D40.C, J118.1, J119.1, J120.3, SUPPLYTIE40.P$1, U40.11
GND40: C81.2, D41.C, J121.1, J122.1, J123.3, SUPPLYTIE41.P$1, U41.11
GND41: C83.2, D42.C, J124.1, J125.1, J126.3, SUPPLYTIE42.P$1, U42.11
GND42: C85.2, D43.C, J127.1, J128.1, J129.3, SUPPLYTIE43.P$1, U43.11
GND43: C87.2, D44.C, J130.1, J131.1, J132.3, SUPPLYTIE44.P$1, U44.11
GND44: C89.2, D45.C, J133.1, J134.1, J135.3, SUPPLYTIE45.P$1, U45.11
GND45: C91.2, D46.C, J136.1, J137.1, J138.3, SUPPLYTIE46.P$1, U46.11
GND46: C93.2, D47.C, J139.1, J140.1, J141.3, SUPPLYTIE47.P$1, U47.11
GND47: C95.2, D48.C, J142.1, J143.1, J144.3, SUPPLYTIE48.P$1, U48.11
unnamed: A0.1, R3.1
unnamed: A1.1, R4.1
unnamed: I2C.3, R1.2
unnamed: I2C1.3, R8.2
unnamed: I2C.1, R2.2
unnamed: I2C1.1, R9.2
unnamed: PWR.1, R5.2
unnamed: R7.2, U1.4
unnamed: D1.A, R5.1
unnamed: A2.1, R10.1
unnamed: A3.1, R11.1
unnamed: D2.A, R12.1
unnamed: R13.2, U2.4
unnamed: PWR1.1, R12.2
unnamed: I2C2.3, R15.2
unnamed: I2C2.1, R16.2
unnamed: A4.1, R17.1
unnamed: A5.1, R18.1
unnamed: D3.A, R19.1
unnamed: R20.2, U3.4
unnamed: PWR2.1, R19.2
unnamed: I2C3.3, R22.2
unnamed: I2C3.1, R23.2
unnamed: A6.1, R24.1
unnamed: A7.1, R25.1
unnamed: D4.A, R26.1
unnamed: R27.2, U4.4
unnamed: PWR3.1, R26.2
unnamed: I2C4.3, R29.2
unnamed: I2C4.1, R30.2
unnamed: A8.1, R31.1
unnamed: A9.1, R32.1
unnamed: D5.A, R33.1
unnamed: R34.2, U5.4
unnamed: PWR4.1, R33.2
unnamed: I2C5.3, R36.2
unnamed: I2C5.1, R37.2
unnamed: A10.1, R38.1
unnamed: A11.1, R39.1
unnamed: D6.A, R40.1
unnamed: R41.2, U6.4
unnamed: PWR5.1, R40.2
unnamed: I2C6.3, R43.2
unnamed: I2C6.1, R44.2
unnamed: A12.1, R45.1
unnamed: A13.1, R46.1
unnamed: D7.A, R47.1
unnamed: R48.2, U7.4
unnamed: PWR6.1, R47.2
unnamed: I2C7.3, R50.2
unnamed: I2C7.1, R51.2
unnamed: A14.1, R52.1
unnamed: A15.1, R53.1
unnamed: D8.A, R54.1
unnamed: R55.2, U8.4
unnamed: PWR7.1, R54.2
unnamed: I2C8.3, R57.2
unnamed: I2C8.1, R58.2
unnamed: A16.1, R59.1
unnamed: A17.1, R60.1
unnamed: D9.A, R61.1
unnamed: R62.2, U9.4
unnamed: PWR8.1, R61.2
unnamed: I2C9.3, R64.2
unnamed: I2C9.1, R65.2
unnamed: A18.1, R66.1
unnamed: A19.1, R67.1
unnamed: D10.A, R68.1
unnamed: R69.2, U10.4
unnamed: PWR9.1, R68.2
unnamed: I2C10.3, R71.2
unnamed: I2C10.1, R72.2
unnamed: A20.1, R73.1
unnamed: A21.1, R74.1
unnamed: D11.A, R75.1
unnamed: R76.2, U11.4
unnamed: PWR10.1, R75.2
unnamed: I2C11.3, R78.2
unnamed: I2C11.1, R79.2
unnamed: A22.1, R80.1
unnamed: A23.1, R81.1
unnamed: D12.A, R82.1
unnamed: R83.2, U12.4
unnamed: PWR11.1, R82.2
unnamed: I2C12.3, R85.2
unnamed: I2C12.1, R86.2
unnamed: A24.1, R87.1
unnamed: A25.1, R88.1
unnamed: D13.A, R89.1
unnamed: R90.2, U13.4
unnamed: PWR12.1, R89.2
unnamed: I2C13.3, R92.2
unnamed: I2C13.1, R93.2
unnamed: A26.1, R94.1
unnamed: A27.1, R95.1
unnamed: D14.A, R96.1
unnamed: R97.2, U14.4
unnamed: PWR13.1, R96.2
unnamed: I2C14.3, R99.2
unnamed: I2C14.1, R100.2
unnamed: A28.1, R101.1
unnamed: A29.1, R102.1
unnamed: D15.A, R103.1
unnamed: R104.2, U15.4
unnamed: PWR14.1, R103.2
unnamed: I2C15.3, R106.2
unnamed: I2C15.1, R107.2
unnamed: A30.1, R108.1
unnamed: A31.1, R109.1
unnamed: D16.A, R110.1
unnamed: R111.2, U16.4
unnamed: PWR15.1, R110.2
unnamed: I2C16.3, R113.2
unnamed: I2C16.1, R114.2
unnamed: A32.1, R115.1
unnamed: A33.1, R116.1
unnamed: D17.A, R117.1
unnamed: R118.2, U17.4
unnamed: PWR16.1, R117.2
unnamed: I2C17.3, R120.2
unnamed: I2C17.1, R121.2
unnamed: A34.1, R122.1
unnamed: A35.1, R123.1
unnamed: D18.A, R124.1
unnamed: R125.2, U18.4
unnamed: PWR17.1, R124.2
unnamed: I2C18.3, R127.2
unnamed: I2C18.1, R128.2
unnamed: A36.1, R129.1
unnamed: A37.1, R130.1
unnamed: D19.A, R131.1
unnamed: R132.2, U19.4
unnamed: PWR18.1, R131.2
unnamed: I2C19.3, R134.2
unnamed: I2C19.1, R135.2
unnamed: A38.1, R136.1
unnamed: A39.1, R137.1
unnamed: D20.A, R138.1
unnamed: R139.2, U20.4
unnamed: PWR19.1, R138.2
unnamed: I2C20.3, R141.2
unnamed: I2C20.1, R142.2
unnamed: A40.1, R143.1
unnamed: A41.1, R144.1
unnamed: D21.A, R145.1
unnamed: R146.2, U21.4
unnamed: PWR20.1, R145.2
unnamed: I2C21.3, R148.2
unnamed: I2C21.1, R149.2
unnamed: A42.1, R150.1
unnamed: A43.1, R151.1
unnamed: D22.A, R152.1
unnamed: R153.2, U22.4
unnamed: PWR21.1, R152.2
unnamed: I2C22.3, R155.2
unnamed: I2C22.1, R156.2
unnamed: A44.1, R157.1
unnamed: A45.1, R158.1
unnamed: D23.A, R159.1
unnamed: R160.2, U23.4
unnamed: PWR22.1, R159.2
unnamed: I2C23.3, R162.2
unnamed: I2C23.1, R163.2
unnamed: A46.1, R164.1
unnamed: A47.1, R165.1
unnamed: D24.A, R166.1
unnamed: R167.2, U24.4
unnamed: PWR23.1, R166.2
unnamed: I2C24.3, R169.2
unnamed: I2C24.1, R170.2
unnamed: A48.1, R171.1
unnamed: A49.1, R172.1
unnamed: D25.A, R173.1
unnamed: R174.2, U25.4
unnamed: PWR24.1, R173.2
unnamed: I2C25.3, R176.2
unnamed: I2C25.1, R177.2
unnamed: A50.1, R178.1
unnamed: A51.1, R179.1
unnamed: D26.A, R180.1
unnamed: R181.2, U26.4
unnamed: PWR25.1, R180.2
unnamed: I2C26.3, R183.2
unnamed: I2C26.1, R184.2
unnamed: A52.1, R185.1
unnamed: A53.1, R186.1
unnamed: D27.A, R187.1
unnamed: R188.2, U27.4
unnamed: PWR26.1, R187.2
unnamed: I2C27.3, R190.2
unnamed: I2C27.1, R191.2
unnamed: A54.1, R192.1
unnamed: A55.1, R193.1
unnamed: D28.A, R194.1
unnamed: R195.2, U28.4
unnamed: PWR27.1, R194.2
unnamed: I2C28.3, R197.2
unnamed: I2C28.1, R198.2
unnamed: A56.1, R199.1
unnamed: A57.1, R200.1
unnamed: D29.A, R201.1
unnamed: R202.2, U29.4
unnamed: PWR28.1, R201.2
unnamed: I2C29.3, R204.2
unnamed: I2C29.1, R205.2
unnamed: A58.1, R206.1
unnamed: A59.1, R207.1
unnamed: D30.A, R208.1
unnamed: R209.2, U30.4
unnamed: PWR29.1, R208.2
unnamed: I2C30.3, R211.2
unnamed: I2C30.1, R212.2
unnamed: A60.1, R213.1
unnamed: A61.1, R214.1
unnamed: D31.A, R215.1
unnamed: R216.2, U31.4
unnamed: PWR30.1, R215.2
unnamed: I2C31.3, R218.2
unnamed: I2C31.1, R219.2
unnamed: A62.1, R220.1
unnamed: A63.1, R221.1
unnamed: D32.A, R222.1
unnamed: R223.2, U32.4
unnamed: PWR31.1, R222.2
unnamed: I2C32.3, R225.2
unnamed: I2C32.1, R226.2
unnamed: A64.1, R227.1
unnamed: A65.1, R228.1
unnamed: D33.A, R229.1
unnamed: R230.2, U33.4
unnamed: PWR32.1, R229.2
unnamed: I2C33.3, R232.2
unnamed: I2C33.1, R233.2
unnamed: A66.1, R234.1
unnamed: A67.1, R235.1
unnamed: D34.A, R236.1
unnamed: R237.2, U34.4
unnamed: PWR33.1, R236.2
unnamed: I2C34.3, R239.2
unnamed: I2C34.1, R240.2
unnamed: A68.1, R241.1
unnamed: A69.1, R242.1
unnamed: D35.A, R243.1
unnamed: R244.2, U35.4
unnamed: PWR34.1, R243.2
unnamed: I2C35.3, R246.2
unnamed: I2C35.1, R247.2
unnamed: A70.1, R248.1
unnamed: A71.1, R249.1
unnamed: D36.A, R250.1
unnamed: R251.2, U36.4
unnamed: PWR35.1, R250.2
unnamed: I2C36.3, R253.2
unnamed: I2C36.1, R254.2
unnamed: A72.1, R255.1
unnamed: A73.1, R256.1
unnamed: D37.A, R257.1
unnamed: R258.2, U37.4
unnamed: PWR36.1, R257.2
unnamed: I2C37.3, R260.2
unnamed: I2C37.1, R261.2
unnamed: A74.1, R262.1
unnamed: A75.1, R263.1
unnamed: D38.A, R264.1
unnamed: R265.2, U38.4
unnamed: PWR37.1, R264.2
unnamed: I2C38.3, R267.2
unnamed: I2C38.1, R268.2
unnamed: A76.1, R269.1
unnamed: A77.1, R270.1
unnamed: D39.A, R271.1
unnamed: R272.2, U39.4
unnamed: PWR38.1, R271.2
unnamed: I2C39.3, R274.2
unnamed: I2C39.1, R275.2
unnamed: A78.1, R276.1
unnamed: A79.1, R277.1
unnamed: D40.A, R278.1
unnamed: R279.2, U40.4
unnamed: PWR39.1, R278.2
unnamed: I2C40.3, R281.2
unnamed: I2C40.1, R282.2
unnamed: A80.1, R283.1
unnamed: A81.1, R284.1
unnamed: D41.A, R285.1
unnamed: R286.2, U41.4
unnamed: PWR40.1, R285.2
unnamed: I2C41.3, R288.2
unnamed: I2C41.1, R289.2
unnamed: A82.1, R290.1
unnamed: A83.1, R291.1
unnamed: D42.A, R292.1
unnamed: R293.2, U42.4
unnamed: PWR41.1, R292.2
unnamed: I2C42.3, R295.2
unnamed: I2C42.1, R296.2
unnamed: A84.1, R297.1
unnamed: A85.1, R298.1
unnamed: D43.A, R299.1
unnamed: R300.2, U43.4
unnamed: PWR42.1, R299.2
unnamed: I2C43.3, R302.2
unnamed: I2C43.1, R303.2
unnamed: A86.1, R304.1
unnamed: A87.1, R305.1
unnamed: D44.A, R306.1
unnamed: R307.2, U44.4
unnamed: PWR43.1, R306.2
unnamed: I2C44.3, R309.2
unnamed: I2C44.1, R310.2
unnamed: A88.1, R311.1
unnamed: A89.1, R312.1
unnamed: D45.A, R313.1
unnamed: R314.2, U45.4
unnamed: PWR44.1, R313.2
unnamed: I2C45.3, R316.2
unnamed: I2C45.1, R317.2
unnamed: A90.1, R318.1
unnamed: A91.1, R319.1
unnamed: D46.A, R320.1
unnamed: R321.2, U46.4
unnamed: PWR45.1, R320.2
unnamed: I2C46.3, R323.2
unnamed: I2C46.1, R324.2
unnamed: A92.1, R325.1
unnamed: A93.1, R326.1
unnamed: D47.A, R327.1
unnamed: R328.2, U47.4
unnamed: PWR46.1, R327.2
unnamed: I2C47.3, R330.2
unnamed: I2C47.1, R331.2
unnamed: A94.1, R332.1
unnamed: A95.1, R333.1
unnamed: D48.A, R334.1
unnamed: R335.2, U48.4
unnamed: PWR47.1, R334.2
READY/INT: J3.2, U1.9
READY/INT1: J6.2, U2.9
READY/INT2: J9.2, U3.9
READY/INT3: J12.2, U4.9
READY/INT4: J15.2, U5.9
READY/INT5: J18.2, U6.9
READY/INT6: J21.2, U7.9
READY/INT7: J24.2, U8.9
READY/INT8: J27.2, U9.9
READY/INT9: J30.2, U10.9
READY/INT10: J33.2, U11.9
READY/INT11: J36.2, U12.9
READY/INT12: J39.2, U13.9
READY/INT13: J42.2, U14.9
READY/INT14: J45.2, U15.9
READY/INT15: J48.2, U16.9
READY/INT16: J51.2, U17.9
READY/INT17: J54.2, U18.9
READY/INT18: J57.2, U19.9
READY/INT19: J60.2, U20.9
READY/INT20: J63.2, U21.9
READY/INT21: J66.2, U22.9
READY/INT22: J69.2, U23.9
READY/INT23: J72.2, U24.9
READY/INT24: J75.2, U25.9
READY/INT25: J78.2, U26.9
READY/INT26: J81.2, U27.9
READY/INT27: J84.2, U28.9
READY/INT28: J87.2, U29.9
READY/INT29: J90.2, U30.9
READY/INT30: J93.2, U31.9
READY/INT31: J96.2, U32.9
READY/INT32: J99.2, U33.9
READY/INT33: J102.2, U34.9
READY/INT34: J105.2, U35.9
READY/INT35: J108.2, U36.9
READY/INT36: J111.2, U37.9
READY/INT37: J114.2, U38.9
READY/INT38: J117.2, U39.9
READY/INT39: J120.2, U40.9
READY/INT40: J123.2, U41.9
READY/INT41: J126.2, U42.9
READY/INT42: J129.2, U43.9
READY/INT43: J132.2, U44.9
READY/INT44: J135.2, U45.9
READY/INT45: J138.2, U46.9
READY/INT46: J141.2, U47.9
READY/INT47: J144.2, U48.9
SCL: J1.4, J2.4, J3.6, R1.1, U1.13
SCL1: J4.4, J5.4, J6.6, R8.1, U2.13
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
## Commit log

2023-09-11 Add v01 protos.
2023-09-12 v01 ready for review
2023-09-12 Update datasheet to latest.
2023-09-14 Pushing to v10
    Panelize and push to v10.
2023-09-14 Remove unneeded folders and add production files.
2023-10-26 Initial docs commit
    Initial commit for GH pages content.
2023-11-10 Update README.md
    Updating README.md from template.
2023-11-14 Update README.md
    Fix extra table row.
2023-11-16 Docs update
    Updating documentation. Added photos & other assets. Minor updates to content.
2023-11-29 Update docs
    Updating examples section & proofreading edits.
2023-12-06 Update introduction.md
    Fixing Qwiic image
2023-12-06 Page deploy fix
    Should fix the page build errors.
2023-12-06 Deploy Fix 2
    Fixing leftover errors from template. Deploy fix #2.
2023-12-06 Deploy Fix 3
    Found what should be the error. Missing workflow item and somehow the readme was saved there instead.
2023-12-07 Examples update
    Adding code snippets for examples & screenshot of serial printout.
2023-12-07 Deployed 55dc6ce with MkDocs version: 1.5.3
2024-10-25 Update mkdocs.yml
    Analytics update.
2024-10-25 Deployed ccab100 with MkDocs version: 1.6.1
